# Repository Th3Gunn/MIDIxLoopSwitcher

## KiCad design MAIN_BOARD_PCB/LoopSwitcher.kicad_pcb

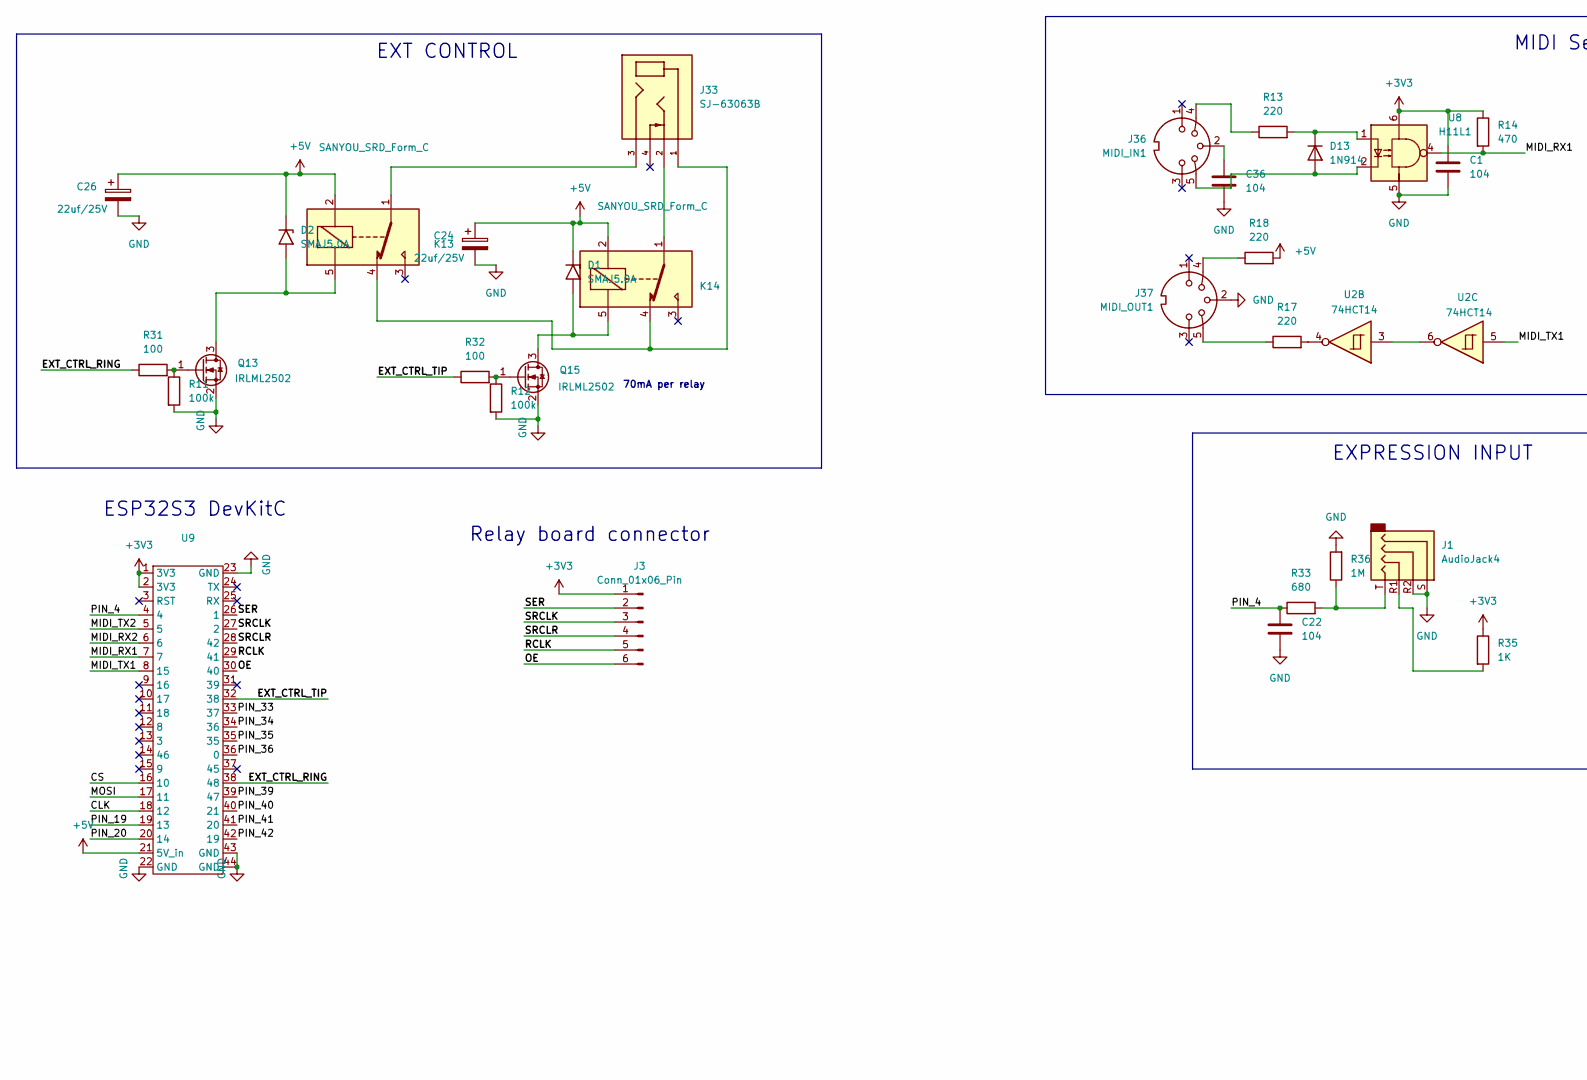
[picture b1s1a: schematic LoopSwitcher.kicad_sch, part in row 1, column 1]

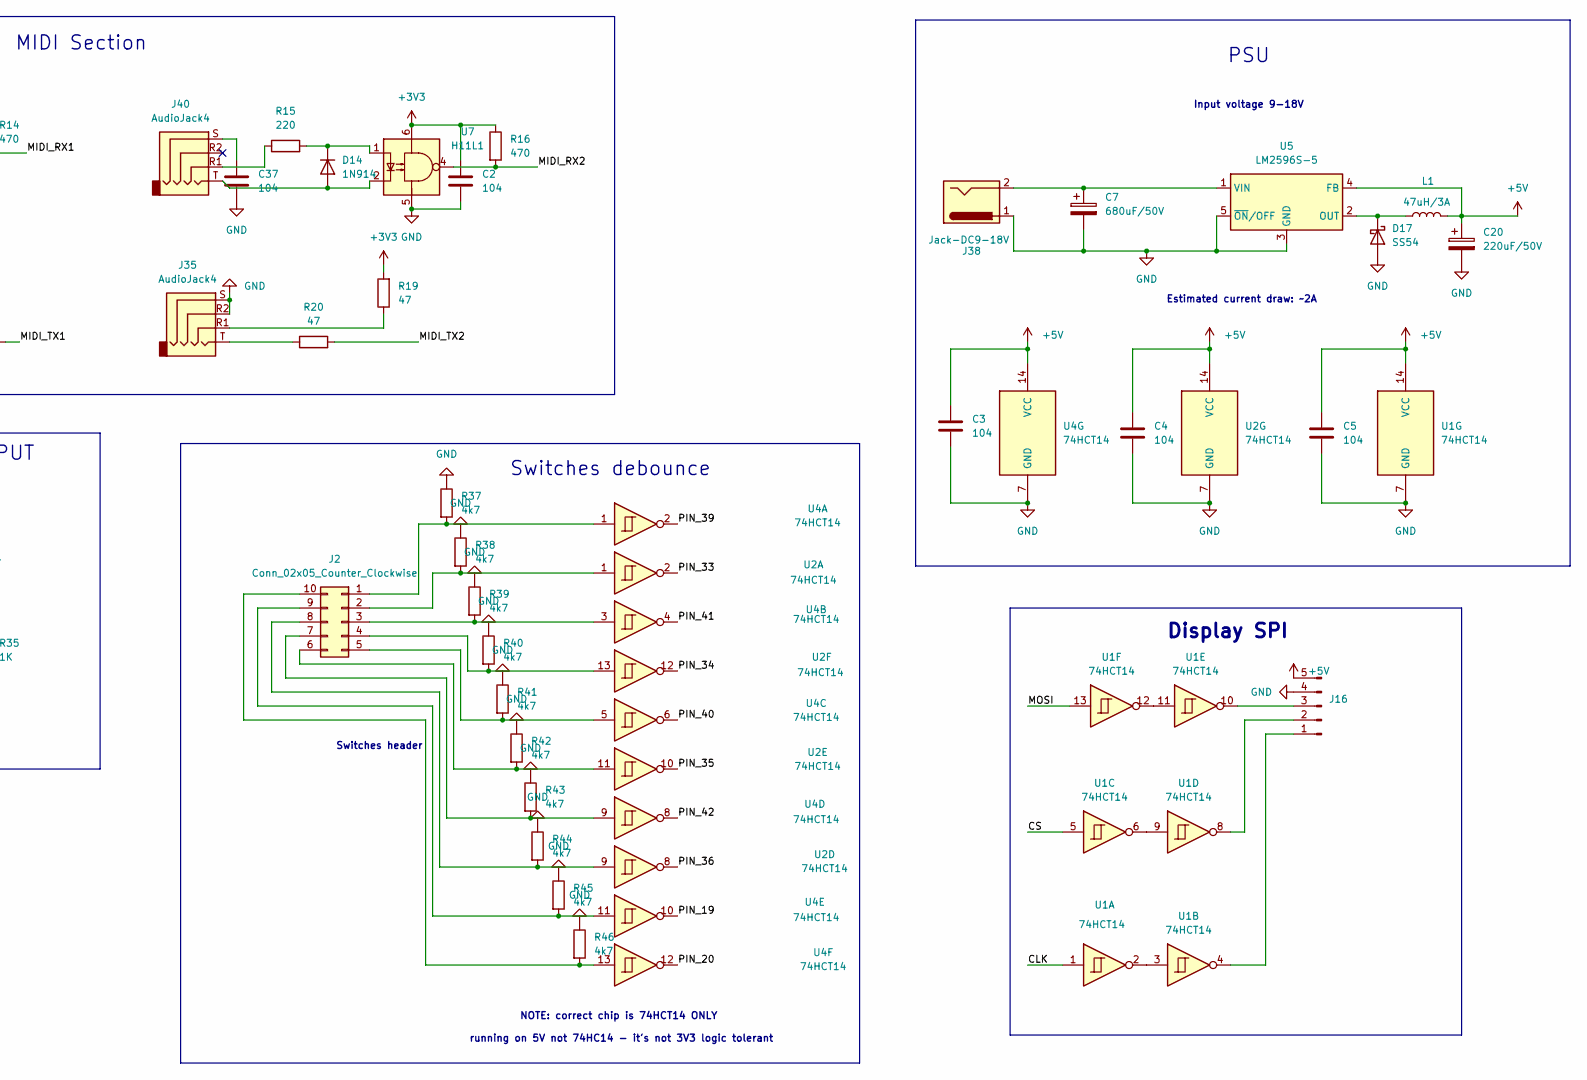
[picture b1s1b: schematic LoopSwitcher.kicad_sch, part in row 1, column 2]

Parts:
C1, C2, C3, C4, C5, C22, C36, C37: 104; C_0603_1608Metric_Pad1.08x0.95mm_HandSolder
C7: 680uF/50V; CP_Radial_D8.0mm_P3.50mm
C20: 220uF/50V; CP_Radial_D8.0mm_P3.50mm
C24, C26: 22uf/25V; CP_Radial_D6.3mm_P2.50mm
D1, D2: SMAJ5.0A; D_SMA
D13, D14: 1N914; D_DO-35_SOD27_P7.62mm_Horizontal
D17: SS54; D_SMC-RM10_Universal_Handsoldering
J1, J35, J40: AudioJack4; Jack_3.5mm_PJ320A_Horizontal
J2: Conn_02x05_Counter_Clockwise; PinHeader_2x05_P2.54mm_Vertical
J3: Conn_01x06_Pin; PinHeader_1x06_P2.54mm_Vertical
J16: Conn_01x05_Pin; PinHeader_1x05_P2.54mm_Vertical
J33: SJ-63063B; CUI_SJ-63063B; PARTREV 1.0
J36: MIDI_IN1; DIN5_MIDI
J37: MIDI_OUT1; DIN5_MIDI
J38: Jack-DC9-18V; BarrelJack_GCT_DCJ200-10-A_Horizontal
K13, K14: SANYOU_SRD_Form_C; Relay_SPDT_SANYOU_SRD_Series_Form_C
L1: 47uH/3A; L_Toroid_Vertical_L25.4mm_W14.7mm_P12.20mm_Vishay_TJ5
Q13, Q15: IRLML2502; SOT-23
R11, R12: 100k; R_0603_1608Metric_Pad0.98x0.95mm_HandSolder
R13, R15, R17, R18: 220; R_0603_1608Metric_Pad0.98x0.95mm_HandSolder
R14, R16: 470; R_0603_1608Metric_Pad0.98x0.95mm_HandSolder
R19, R20: 47; R_0603_1608Metric_Pad0.98x0.95mm_HandSolder
R31, R32: 100; R_0603_1608Metric_Pad0.98x0.95mm_HandSolder
R33: 680; R_0603_1608Metric_Pad0.98x0.95mm_HandSolder
R35: 1K; R_0603_1608Metric_Pad0.98x0.95mm_HandSolder
R36: 1M; R_0603_1608Metric_Pad0.98x0.95mm_HandSolder
R37, R38, R39, R40, R41, R42, R43, R44, R45, R46: 4k7; R_0603_1608Metric_Pad0.98x0.95mm_HandSolder
U1, U2, U4: 74HCT14; SOIC-14_3.9x8.7mm_P1.27mm
U5: LM2596S-5; TO-263-5_TabPin3
U7, U8: H11L1; DIP-6_W7.62mm_LongPads
U9: ESP32S3_1

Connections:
+3V3: C1.1, C2.1, J3.1, R14.1, R16.1, R19.2, R35.1, U7.6, U8.6, U9.1 (3V3), U9.2 (3V3)
+5V: C3.1, C4.1, C5.1, C20.1, C24.1, C26.1, D1.1 (A1), D2.1 (A1), J16.5, K13.2, K14.2, L1.2, R18.2, U1.14 (VCC), U2.14 (VCC), U4.14 (VCC), U5.4 (FB), U9.21 (5V_in)
/<NO NET>: U4.4, U9.41 (20)
/CLK: U1.1, U9.18 (12)
/CS: U1.5, U9.16 (10)
/EXT_CTRL_RING: R31.1, U9.38 (48)
/EXT_CTRL_TIP: R32.1, U9.32 (38)
/MIDI_RX1: R14.2, U8.4, U9.7
/MIDI_RX2: R16.2, U7.4, U9.6
/MIDI_TX1: U2.5, U9.8 (15)
/MIDI_TX2: R20.2, U9.5
/MOSI: U1.13, U9.17 (11)
/OE: J3.6, U9.30 (40)
/PIN_4: C22.2, R33.1, U9.4
/PIN_19: U4.10, U9.19 (13)
/PIN_20: U4.12, U9.20 (14)
/PIN_33: U2.2, U9.33 (37)
/PIN_34: U2.12, U9.34 (36)
/PIN_35: U2.10, U9.35
/PIN_36: U2.8, U9.36 (0)
/PIN_39: U4.2, U9.39 (47)
/PIN_40: U4.6, U9.40 (21)
/PIN_42: U4.8, U9.42 (19)
/RCLK: J3.5, U9.29 (41)
/SER: J3.2, U9.26 (1)
/SRCLK: J3.3, U9.27 (2)
/SRCLR: J3.4, U9.28 (42)
GND: C1.2, C2.2, C3.2, C4.2, C5.2, C7.2, C20.2, C22.1, C24.2, C26.2, C36.1, C37.1, D17.2 (A), J1.R2, J1.S, J16.4, J35.R2, J35.S, J37.2, J38.1, Q13.2 (S), Q15.2 (S), R11.2, R12.2, R36.2, R37.1, R38.1, R39.1, R40.1, R41.1, R42.1, R43.1, R44.1, R45.1, R46.1, U1.7 (GND), U2.7 (GND), U4.7 (GND), U5.3 (GND), U5.5 (~ON/OFF), U7.5, U8.5, U9.22 (GND), U9.23 (GND), U9.43 (GND), U9.44 (GND)
unnamed: C36.2, J36.2
unnamed: C37.2, J40.S
unnamed: D1.2 (A2), K14.5, Q15.3 (D)
unnamed: D2.2 (A2), K13.5, Q13.3 (D)
unnamed: D13.2 (A), J36.5, U8.2
unnamed: D13.1 (K), R13.2, U8.1
unnamed: D14.2 (A), J40.T, U7.2
unnamed: D14.1 (K), R15.2, U7.1
unnamed: D17.1 (K), L1.1, U5.2 (OUT)
unnamed: J1.R1, R35.2
unnamed: J1.T, R33.2, R36.1
unnamed: J2.1, R37.2, U4.1
unnamed: J2.2, R38.2, U2.1
unnamed: J2.3, R39.2, U4.3
unnamed: J2.4, R40.2, U2.13
unnamed: J2.5, R41.2, U4.5
unnamed: J2.6, R42.2, U2.11
unnamed: J2.7, R43.2, U4.9
unnamed: J2.8, R44.2, U2.9
unnamed: J2.9, R45.2, U4.11
unnamed: J2.10, R46.2, U4.13
unnamed: J16.1, U1.4
unnamed: J16.2, U1.8
unnamed: J16.3, U1.10
unnamed: J33.1, K13.4, K14.4
unnamed: J33.2, K14.1
unnamed: J33.3, K13.1
unnamed: J35.R1, R19.1
unnamed: J35.T, R20.1
unnamed: J36.4, R13.1
unnamed: J37.4, R18.1
unnamed: J37.5, R17.1
unnamed: J40.R1, R15.1
unnamed: Q13.1 (G), R11.1, R31.2
unnamed: Q15.1 (G), R12.1, R32.2
unnamed: R17.2, U2.4
unnamed: U1.2, U1.3
unnamed: U1.6, U1.9
unnamed: U1.11, U1.12
unnamed: U2.3, U2.6
unnamed: C7.1, J38.2, U5.1 (VIN)

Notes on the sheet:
Estimated current draw: ~2A
EXT CONTROL
Display SPI
EXPRESSION INPUT
Input voltage 9-18V
NOTE: correct chip is 74HCT14 ONLY running on 5V not 74HC14 - it's not 3V3 logic tolerant
Relay board connector
MIDI Section
Switches header
70mA per relay
Switches debounce
ESP32S3 DevKitC
PSU

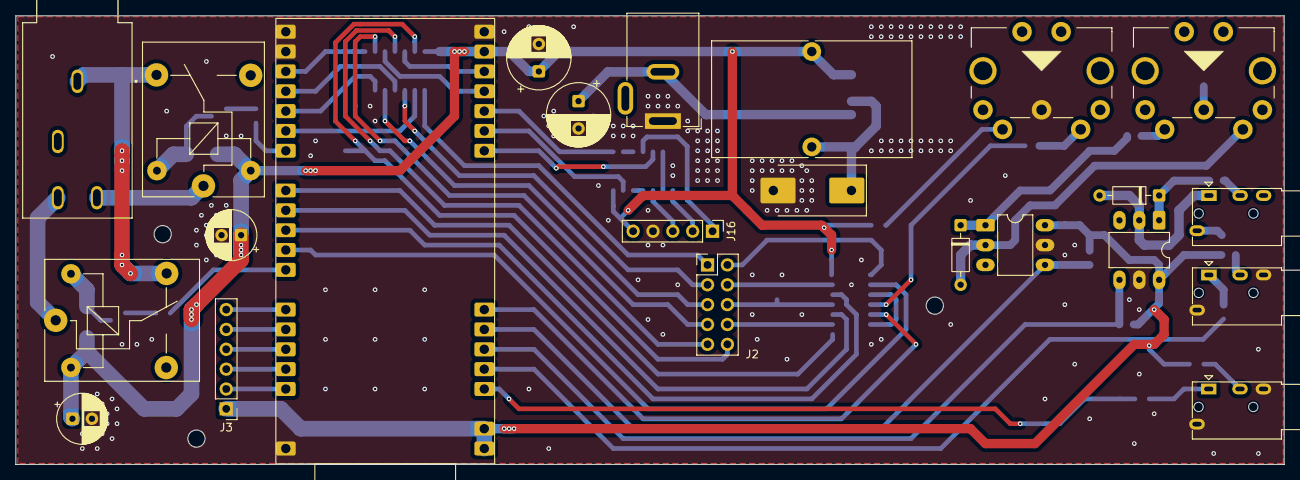
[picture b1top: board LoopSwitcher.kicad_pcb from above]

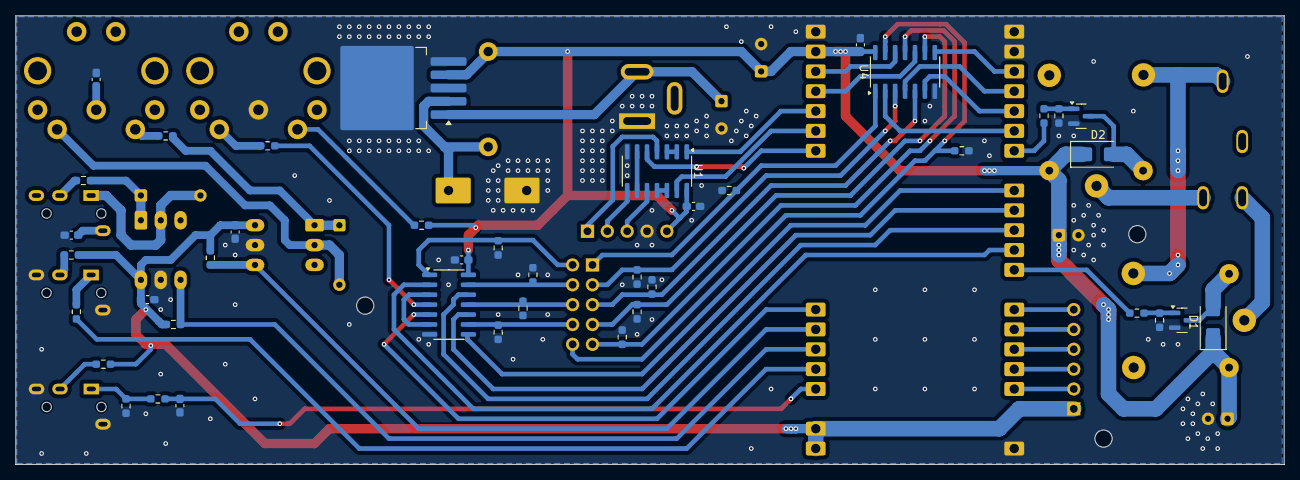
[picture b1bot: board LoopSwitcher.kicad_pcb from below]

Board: 2 copper layers, 162.3 x 57.4 mm, 64 parts (41 on the bottom side), 69 nets.

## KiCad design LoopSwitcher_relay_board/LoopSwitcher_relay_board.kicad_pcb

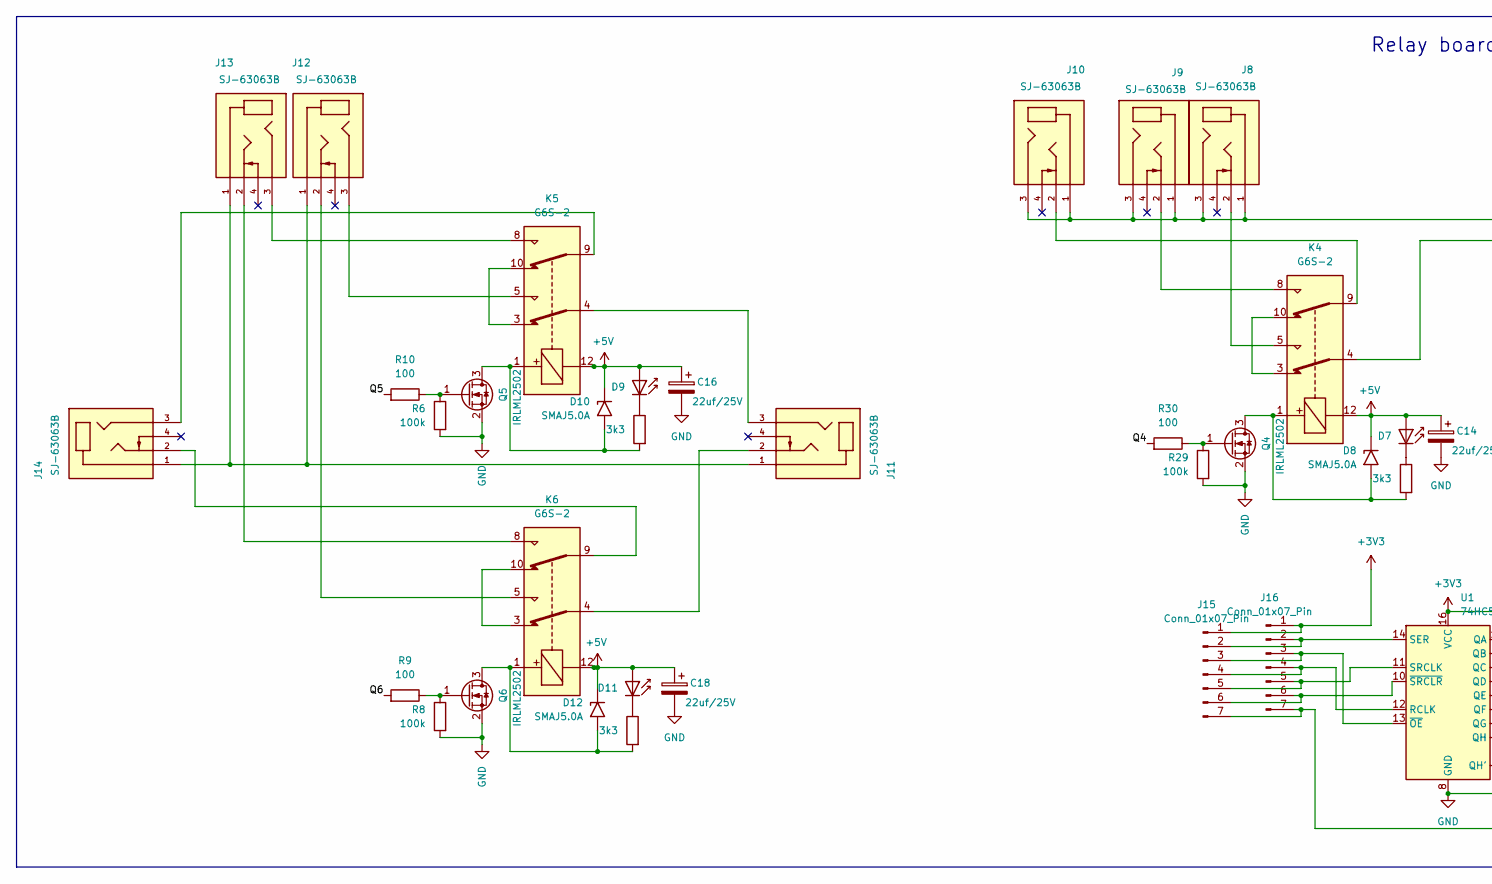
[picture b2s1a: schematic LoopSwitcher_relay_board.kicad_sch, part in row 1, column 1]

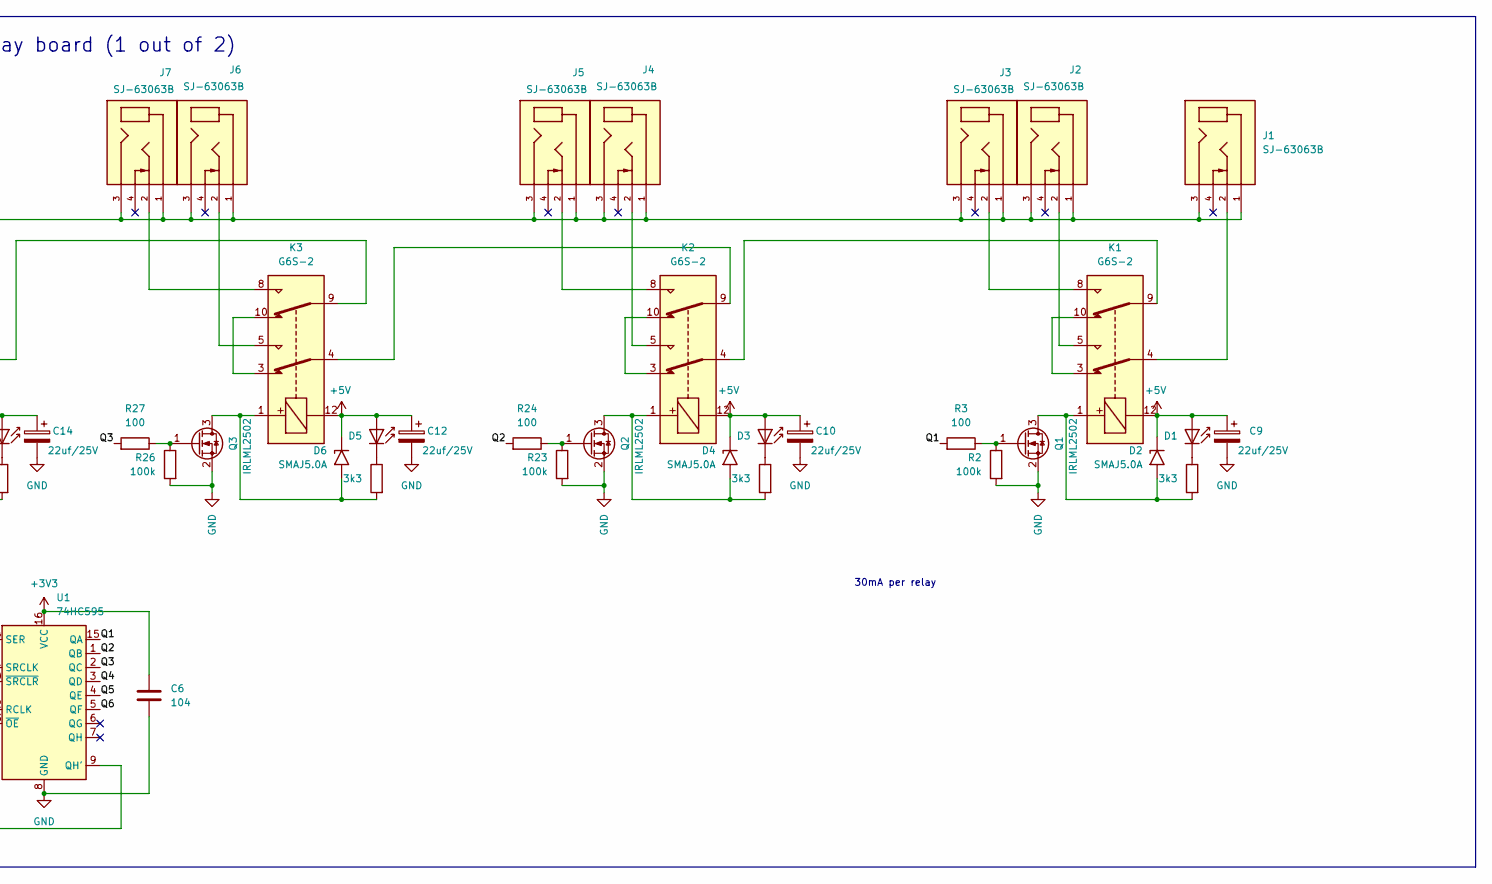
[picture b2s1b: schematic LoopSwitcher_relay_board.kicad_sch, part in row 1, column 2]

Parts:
C6: 104; C_0603_1608Metric_Pad1.08x0.95mm_HandSolder
C9, C10, C12, C14, C16, C18: 22uf/25V; CP_Radial_D6.3mm_P2.50mm
D1, D3, D5, D7, D9, D11: IR204A; LED_D3.0mm_IRBlack
D2, D4, D6, D8, D10, D12: SMAJ5.0A; D_SMA
J1, J2, J3, J4, J5, J6, J7, J8, J9, J10, J11, J12, J13, J14: SJ-63063B; CUI_SJ-63063B; PARTREV 1.0
J15, J16: Conn_01x07_Pin; PinHeader_1x07_P2.54mm_Vertical
K1, K2, K3, K4, K5, K6: G6S-2; Relay_DPDT_Omron_G6S-2
Q1, Q2, Q3, Q4, Q5, Q6: IRLML2502; SOT-23
R1, R4, R5, R7, R25, R28: 3k3; R_0603_1608Metric_Pad0.98x0.95mm_HandSolder
R2, R6, R8, R23, R26, R29: 100k; R_0603_1608Metric_Pad0.98x0.95mm_HandSolder
R3, R9, R10, R24, R27, R30: 100; R_0603_1608Metric_Pad0.98x0.95mm_HandSolder
U1: 74HC595; SOP-16_4.4x10.4mm_P1.27mm

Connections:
+3V3: C6.1, J15.1, J16.1, U1.16 (VCC)
+5V: C9.1, C10.1, C12.1, C14.1, C16.1, C18.1, D1.2 (A), D2.1 (A1), D3.2 (A), D4.1 (A1), D5.2 (A), D6.1 (A1), D7.2 (A), D8.1 (A1), D9.2 (A), D10.1 (A1), D11.2 (A), D12.1 (A1), K1.12, K2.12, K3.12, K4.12, K5.12, K6.12
/Q1: R3.2, U1.15 (QA)
/Q2: R24.2, U1.1 (QB)
/Q3: R27.2, U1.2 (QC)
/Q4: R30.2, U1.3 (QD)
/Q5: R10.2, U1.4 (QE)
/Q6: R9.2, U1.5 (QF)
GND: C6.2, C9.2, C10.2, C12.2, C14.2, C16.2, C18.2, Q1.2 (S), Q2.2 (S), Q3.2 (S), Q4.2 (S), Q5.2 (S), Q6.2 (S), R2.2, R6.2, R8.2, R23.2, R26.2, R29.2, U1.8 (GND)
unnamed: D1.1 (K), R1.1
unnamed: D2.2 (A2), K1.1, Q1.3 (D), R1.2
unnamed: D3.1 (K), R4.1
unnamed: D4.2 (A2), K2.1, Q2.3 (D), R4.2
unnamed: D5.1 (K), R25.1
unnamed: D6.2 (A2), K3.1, Q3.3 (D), R25.2
unnamed: D7.1 (K), R28.1
unnamed: D8.2 (A2), K4.1, Q4.3 (D), R28.2
unnamed: D9.1 (K), R5.1
unnamed: D10.2 (A2), K5.1, Q5.3 (D), R5.2
unnamed: D11.1 (K), R7.1
unnamed: D12.2 (A2), K6.1, Q6.3 (D), R7.2
unnamed: J1.1, J1.3, J2.1, J2.3, J3.1, J3.3, J4.1, J4.3, J5.1, J5.3, J6.1, J6.3, J7.1, J7.3, J8.1, J8.3, J9.1, J9.3, J10.1, J10.3
unnamed: J1.2, K1.4
unnamed: J2.2, K1.5
unnamed: J3.2, K1.8
unnamed: J4.2, K2.5
unnamed: J5.2, K2.8
unnamed: J6.2, K3.5
unnamed: J7.2, K3.8
unnamed: J8.2, K4.5
unnamed: J9.2, K4.8
unnamed: J10.2, K4.9
unnamed: J11.1, J12.1, J13.1, J14.1
unnamed: J11.2, K6.4
unnamed: J11.3, K5.4
unnamed: J12.2, K6.5
unnamed: J12.3, K5.5
unnamed: J13.2, K6.8
unnamed: J13.3, K5.8
unnamed: J14.2, K6.9
unnamed: J14.3, K5.9
unnamed: J15.2, J16.2, U1.14 (SER)
unnamed: J15.3, J16.3, U1.13 (~OE)
unnamed: J15.4, J16.4, U1.12 (RCLK)
unnamed: J15.5, J16.5, U1.11 (SRCLK)
unnamed: J15.6, J16.6, U1.10 (~SRCLR)
unnamed: J15.7, J16.7, U1.9 (QH')
unnamed: K1.9, K2.4
unnamed: K1.3, K1.10
unnamed: K2.9, K3.4
unnamed: K2.3, K2.10
unnamed: K3.9, K4.4
unnamed: K3.3, K3.10
unnamed: K4.3, K4.10
unnamed: K5.3, K5.10
unnamed: K6.3, K6.10
unnamed: Q1.1 (G), R2.1, R3.1
unnamed: Q2.1 (G), R23.1, R24.1
unnamed: Q3.1 (G), R26.1, R27.1
unnamed: Q4.1 (G), R29.1, R30.1
unnamed: Q5.1 (G), R6.1, R10.1
unnamed: Q6.1 (G), R8.1, R9.1

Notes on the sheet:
Relay board (1 out of 2)
30mA per relay

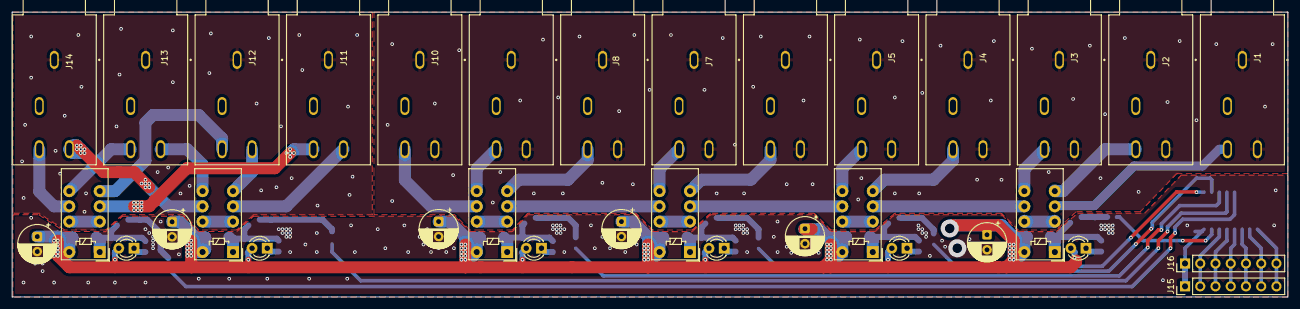
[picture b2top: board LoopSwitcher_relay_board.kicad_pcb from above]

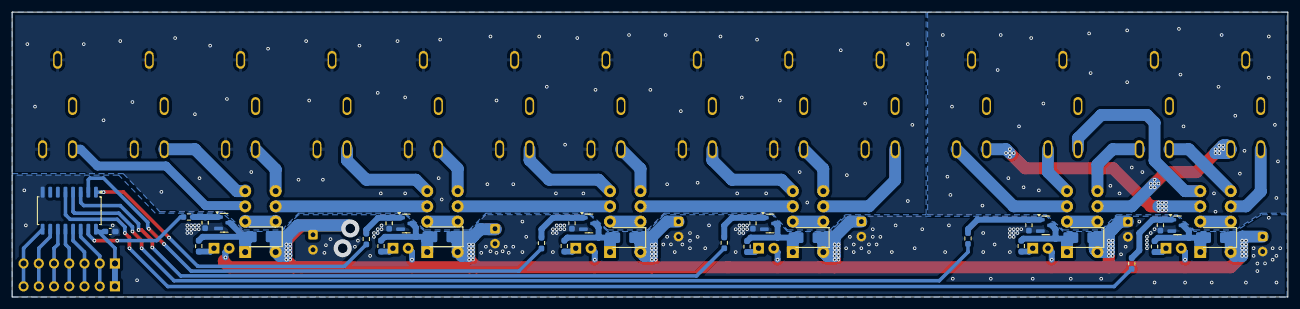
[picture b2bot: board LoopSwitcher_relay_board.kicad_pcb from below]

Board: 2 copper layers, 212.7 x 47.5 mm, 66 parts (32 on the bottom side), 62 nets.

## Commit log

2025-12-31 Initial commit - full reset
2026-01-01 Update .gitignore to include MIDI build directories
2026-01-03 Add MIDI_RX folder from cloned repository
2026-01-03 SPI display control, TODO: delete unnecessary libraries and code from SPI lcd template have used
2026-01-07 Add files via upload
    Should be final revision
2026-01-12 Cleanup
